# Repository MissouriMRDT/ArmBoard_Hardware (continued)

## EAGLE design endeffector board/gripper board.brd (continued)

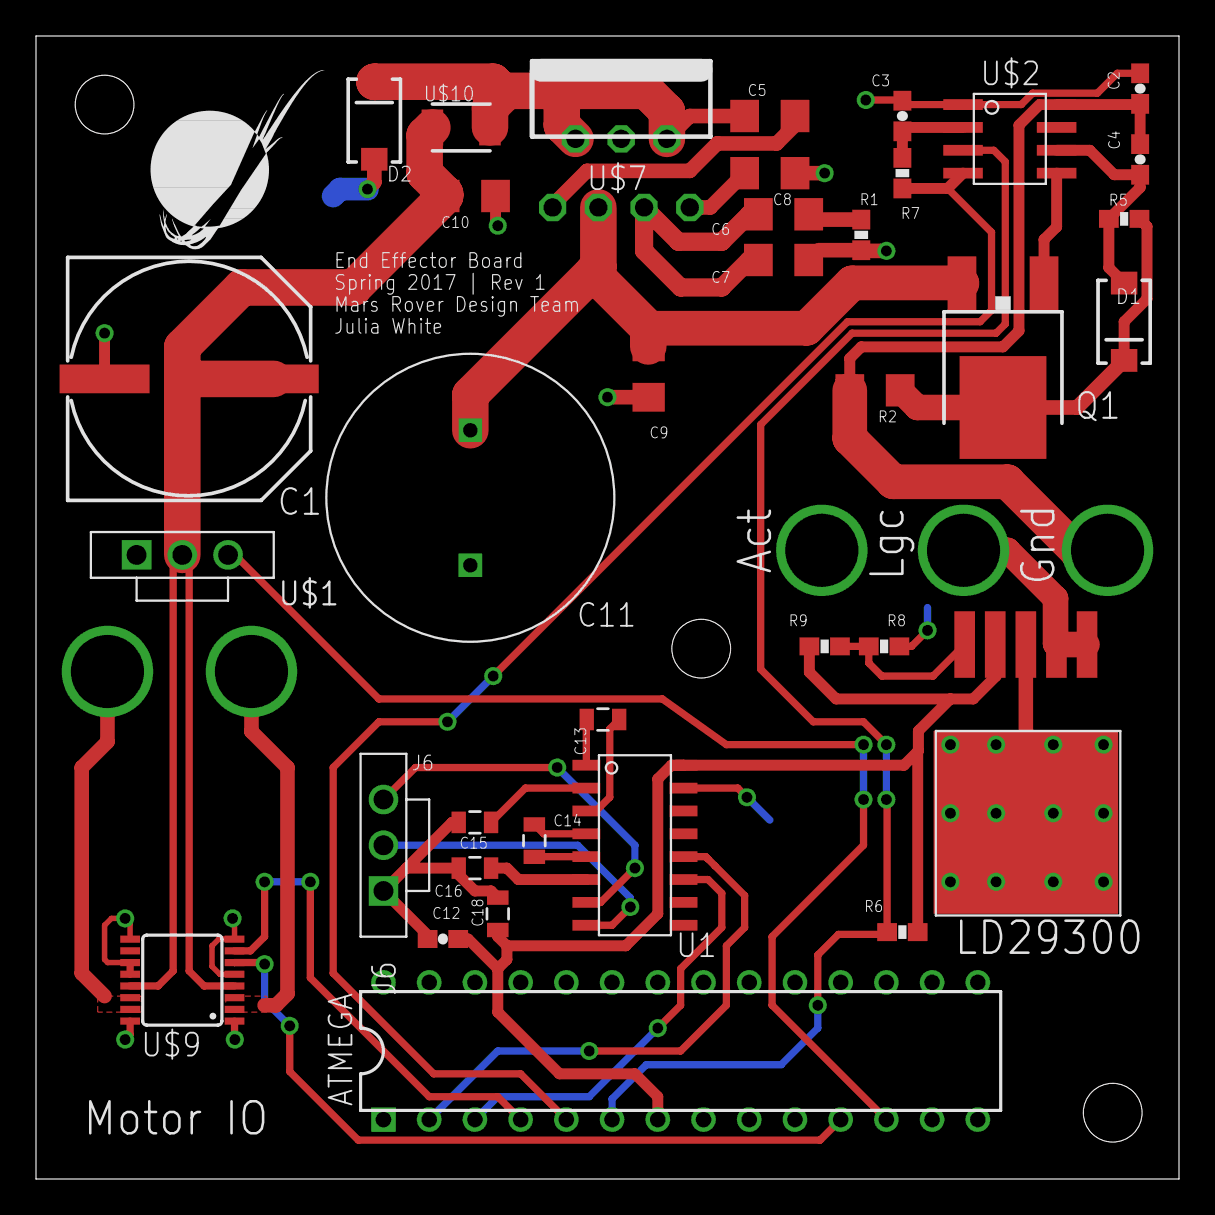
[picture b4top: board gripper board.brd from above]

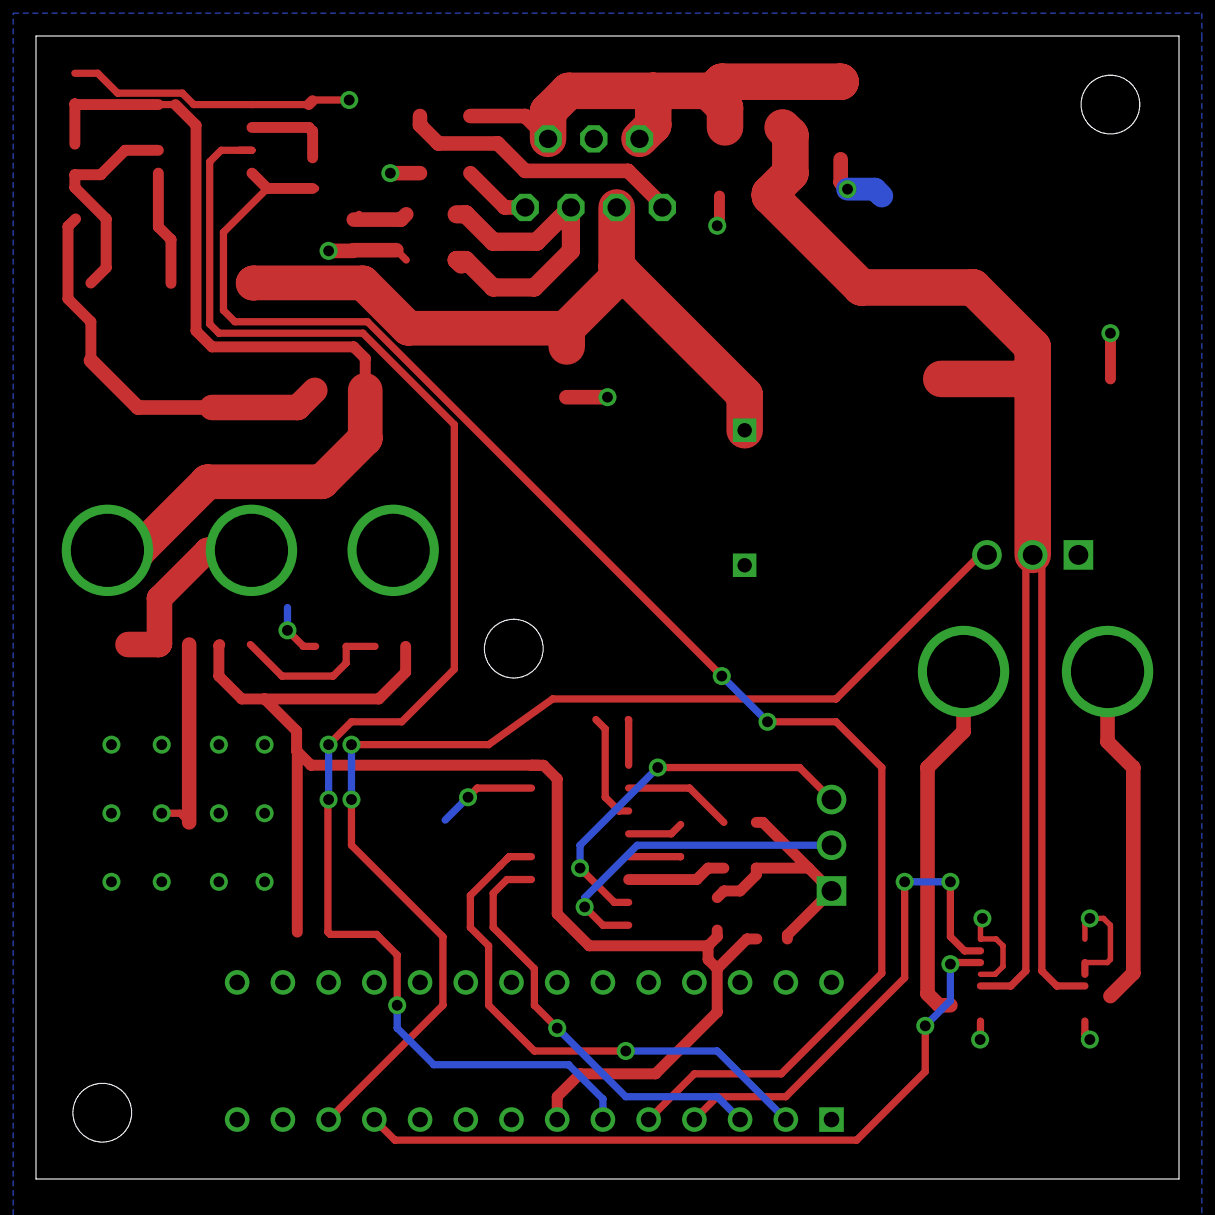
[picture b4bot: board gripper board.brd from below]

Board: 2 copper layers, 63.5 x 63.5 mm, 45 parts (6 on the bottom side), 33 nets.

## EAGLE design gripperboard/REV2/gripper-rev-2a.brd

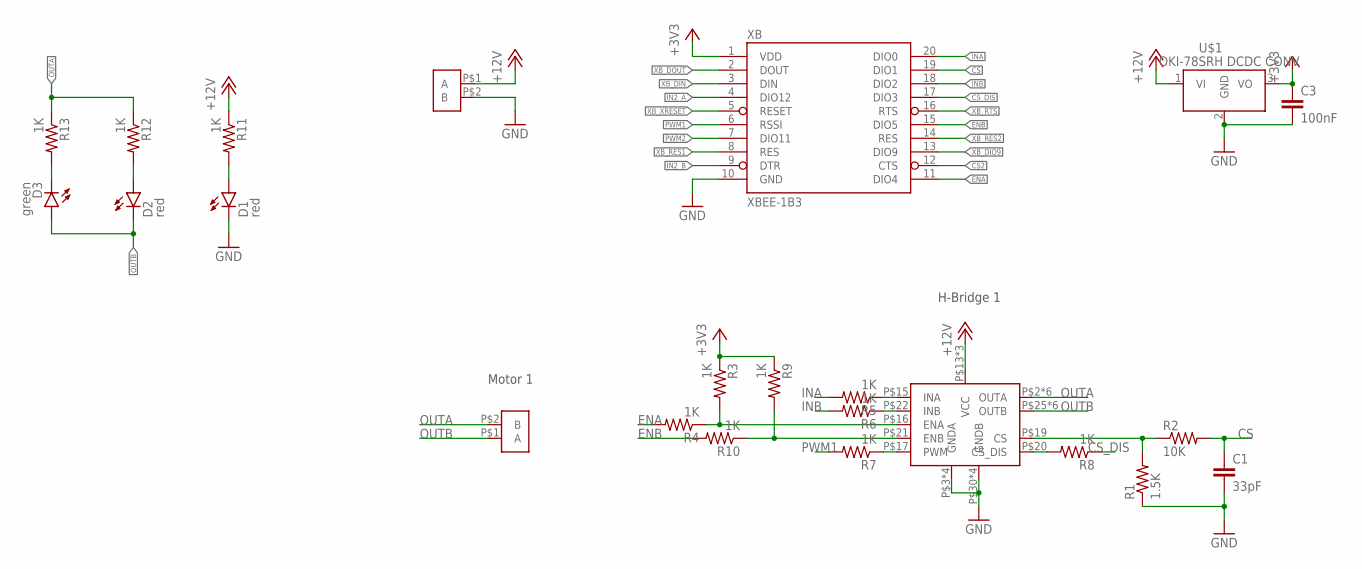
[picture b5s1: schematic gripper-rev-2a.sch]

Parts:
C1: 33pF; 0603-CAP
C3: 100nF; 0603-CAP
D1, D2: red; LED-0603
D3: green; LED-0603
R1: 1.5K; 0603-RES
R2: 10K; 0603-RES
R3, R4, R5, R6, R7, R8, R9, R10, R11, R12, R13: 1K; 0603-RES
U$1: Q_OKI-78SR; OKI-78SR_HORIZ
U$4: VNH5180A; POWERSSO-36_TP
U$6, U$8: TE_2POS_SCREW_TERM; TE_2POS-5MM_SCREW_TERM
XB: XBEE-1B3; XBEE-SMD

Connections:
+3V3: C3.1, R3.1, R9.1, U$1.3 (VO), XB.1 (VDD)
+12V: R11.1, U$1.1 (VI), U$4.P$13 (VCC), U$4.P$24 (VCC), U$4.SLUG1 (VCC), U$6.P$1 (A)
CS: C1.1, R2.2, XB.19 (DIO1)
CS2: XB.12 (CTS)
CS_DIS: R8.1, XB.17 (DIO3)
ENA: R4.2, XB.11 (DIO4)
ENB: R10.2, XB.15 (DIO5)
GND: C1.2, C3.2, D1.C, R1.1, U$1.2 (GND), U$4.P$3 (GNDA), U$4.P$4 (GNDA), U$4.P$6 (GNDA), U$4.P$7 (GNDA), U$4.P$30 (GNDB), U$4.P$31 (GNDB), U$4.P$33 (GNDB), U$4.P$34 (GNDB), U$6.P$2 (B), XB.10 (GND)
IN2_A: XB.4 (DIO12)
IN2_B: XB.9 (DTR)
INA: R5.2, XB.20 (DIO0)
INB: R6.2, XB.18 (DIO2)
unnamed: R5.1, U$4.P$15 (INA)
unnamed: R1.2, R2.1, U$4.P$19 (CS)
unnamed: R6.1, U$4.P$22 (INB)
unnamed: R7.1, U$4.P$17 (PWM)
unnamed: R3.2, R4.1, U$4.P$16 (ENA)
unnamed: R9.2, R10.1, U$4.P$21 (ENB)
unnamed: R8.2, U$4.P$20 (CS_DIS)
unnamed: D1.A, R11.2
unnamed: D2.A, R12.2
unnamed: D3.C, R13.2
OUTA: R12.1, R13.1, U$4.P$2 (OUTA), U$4.P$8 (OUTA), U$4.P$10 (OUTA), U$4.P$11 (OUTA), U$4.P$12 (OUTA), U$4.SLUG2 (OUTA), U$8.P$2 (B)
OUTB: D2.C, D3.A, U$4.P$25 (OUTB), U$4.P$26 (OUTB), U$4.P$27 (OUTB), U$4.P$29 (OUTB), U$4.P$35 (OUTB), U$4.SLUG3 (OUTB), U$8.P$1 (A)
PWM1: R7.2, XB.6 (RSSI)
PWM2: XB.7 (DIO11)
XB_DIN: XB.3 (DIN)
XB_DIO9: XB.13 (DIO9)
XB_RES1: XB.8 (RES)
XB_RES2: XB.14 (RES)
XB_RTS: XB.16 (RTS)
XB_XRESET: XB.5 (RESET)

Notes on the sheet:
H-Bridge 1
Motor 1

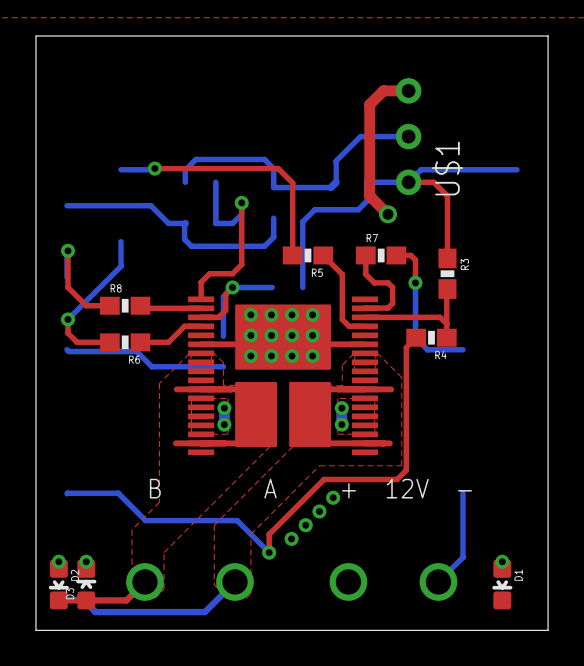
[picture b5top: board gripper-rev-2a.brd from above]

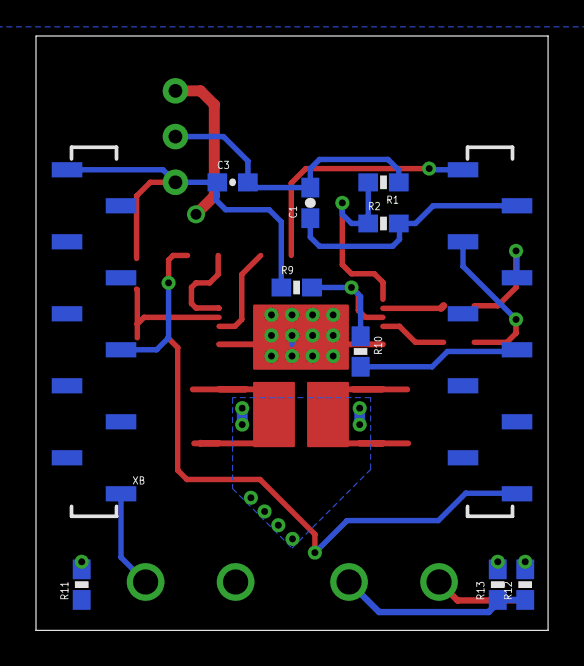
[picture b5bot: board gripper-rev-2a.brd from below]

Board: 2 copper layers, 28.4 x 33.0 mm, 23 parts (10 on the bottom side), 22 nets.

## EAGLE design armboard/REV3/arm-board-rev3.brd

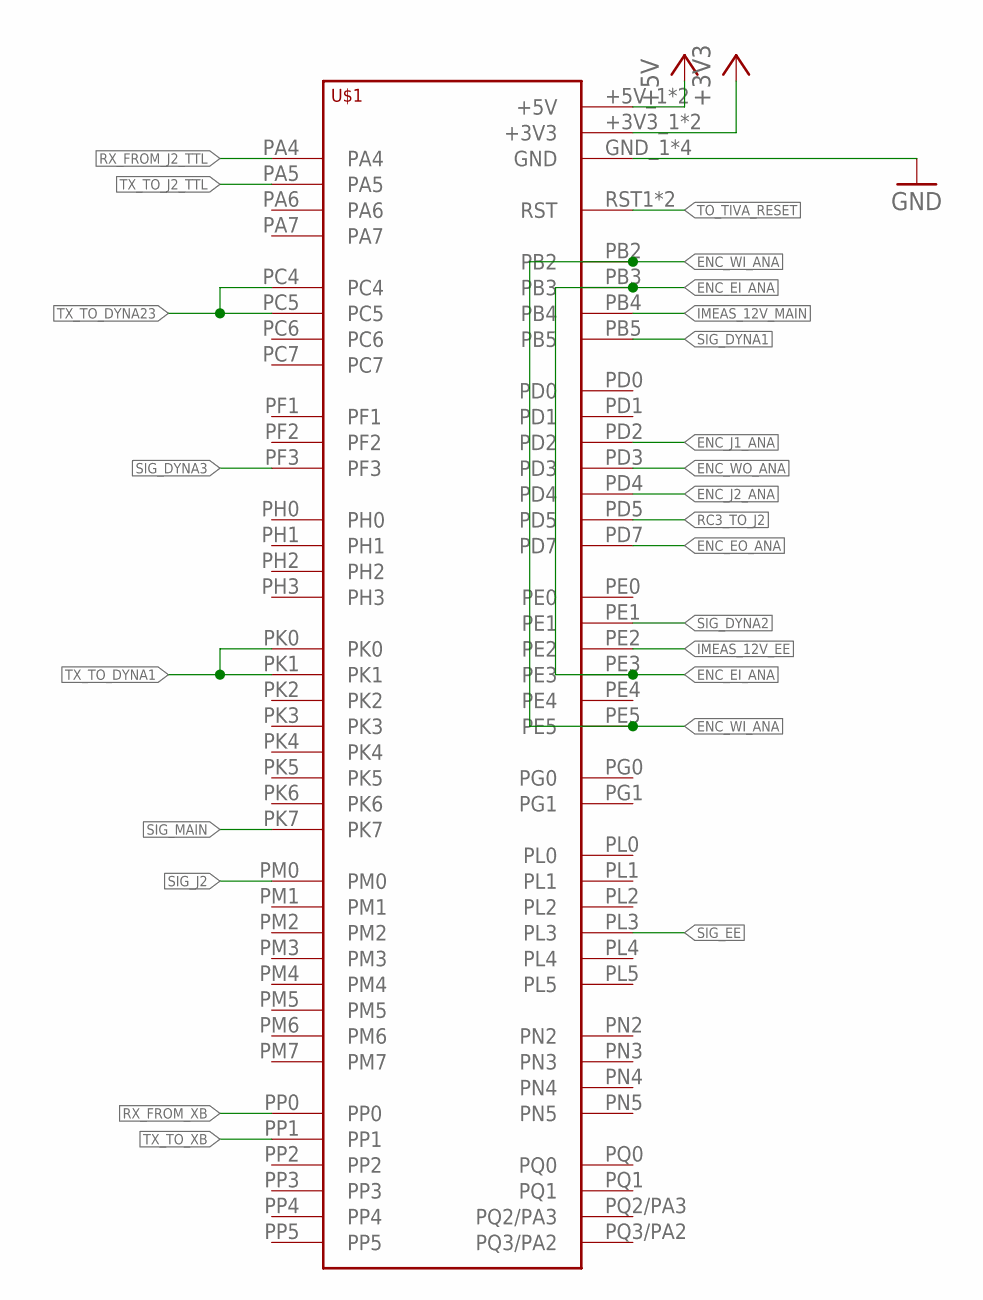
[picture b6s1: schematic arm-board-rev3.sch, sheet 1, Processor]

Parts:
U$1: TIVA-C-CONNECTED

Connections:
+3V3: U$1.+3V3_1 (+3V3), U$1.+3V3_2 (+3V3); also elsewhere on the board
+5V: U$1.+5V_1 (+5V), U$1.+5V_2 (+5V); also elsewhere on the board
ENC_EI_ANA: U$1.PB3, U$1.PE3; also elsewhere on the board
ENC_EO_ANA: U$1.PD7; also elsewhere on the board
ENC_J1_ANA: U$1.PD2; also elsewhere on the board
ENC_J2_ANA: U$1.PD4; also elsewhere on the board
ENC_WI_ANA: U$1.PB2, U$1.PE5; also elsewhere on the board
ENC_WO_ANA: U$1.PD3; also elsewhere on the board
GND: U$1.GND_1 (GND), U$1.GND_2 (GND), U$1.GND_3 (GND), U$1.GND_4 (GND); also elsewhere on the board
IMEAS_12V_EE: U$1.PE2; also elsewhere on the board
IMEAS_12V_MAIN: U$1.PB4; also elsewhere on the board
RC3_TO_J2: U$1.PD5; also elsewhere on the board
RX_FROM_J2_TTL: U$1.PA4; also elsewhere on the board
RX_FROM_XB: U$1.PP0; also elsewhere on the board
SIG_DYNA1: U$1.PB5; also elsewhere on the board
SIG_DYNA2: U$1.PE1; also elsewhere on the board
SIG_DYNA3: U$1.PF3; also elsewhere on the board
SIG_EE: U$1.PL3; also elsewhere on the board
SIG_J2: U$1.PM0; also elsewhere on the board
SIG_MAIN: U$1.PK7; also elsewhere on the board
TO_TIVA_RESET: U$1.RST1 (RST), U$1.RST_2 (RST); also elsewhere on the board
TX_TO_DYNA1: U$1.PK0, U$1.PK1; also elsewhere on the board
TX_TO_DYNA23: U$1.PC4, U$1.PC5; also elsewhere on the board
TX_TO_J2_TTL: U$1.PA5; also elsewhere on the board
TX_TO_XB: U$1.PP1; also elsewhere on the board

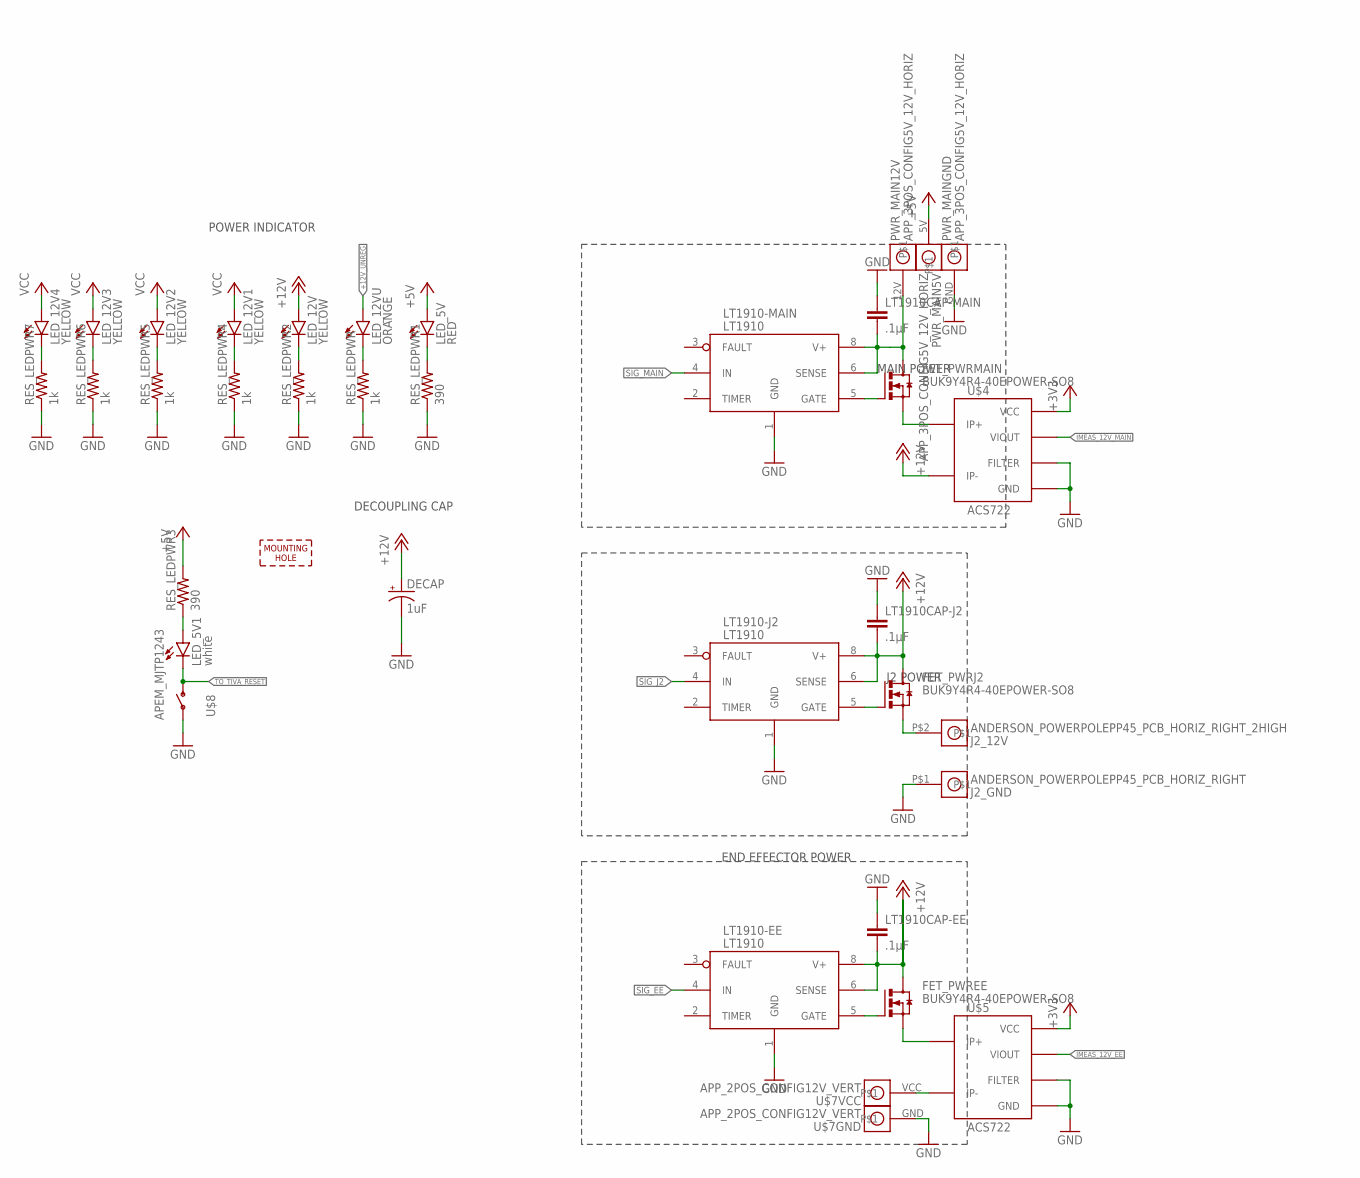
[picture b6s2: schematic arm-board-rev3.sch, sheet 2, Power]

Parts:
DECAP: 1uF; CPOL-RADIAL-100UF-25V
FET_PWREE: BUK9Y4R4-40EPOWER-SO8; POWER-SO8
FET_PWRJ2: BUK9Y4R4-40EPOWER-SO8; POWER-SO8
FET_PWRMAIN: BUK9Y4R4-40EPOWER-SO8; POWER-SO8
J2_12V: ANDERSON_POWERPOLEPP45_PCB_HORIZ_RIGHT_2HIGH; APP45_PCB_HORIZ_RIGHT_2HIGH
J2_GND: ANDERSON_POWERPOLEPP45_PCB_HORIZ_RIGHT; APP45_PCB_HORIZ_RIGHT
LED_5V: RED; LED-0603
LED_5V1: white; LED-1206
LED_12V, LED_12V1, LED_12V2, LED_12V3, LED_12V4: YELLOW; LED-0603
LED_12VU: ORANGE; LED-0603
LT1910-EE, LT1910-J2, LT1910-MAIN: LT1910; SO8
LT1910CAP-EE, LT1910CAP-J2, LT1910CAP-MAIN: .1µF; 0603-CAP
PWR_MAIN: APP_3POS_CONFIG5V_12V_HORIZ; APP45_5V_12V_HORIZ_CONFIG
RES_LEDPWR, RES_LEDPWR2, RES_LEDPWR4, RES_LEDPWR5, RES_LEDPWR6, RES_LEDPWR7: 1k; 0603-RES
RES_LEDPWR1, RES_LEDPWR3: 390; 0603-RES
U$3: MOUNTING_HOLE#6; #6_SCREW
U$4, U$5: ACS722; SO-08
U$7: APP_2POS_CONFIG12V_VERT; APP45_12V_VERT_CONFIG
U$8: APEM_MJTP1243

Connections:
+3V3: U$4.8 (VCC), U$5.8 (VCC); also elsewhere on the board
+5V: LED_5V.A, PWR_MAIN.5V, RES_LEDPWR3.2; also elsewhere on the board
+12V: DECAP.1 (+), FET_PWREE.5 (D), FET_PWREE.6 (D), FET_PWREE.7 (D), FET_PWREE.8 (D), FET_PWRJ2.5 (D), FET_PWRJ2.6 (D), FET_PWRJ2.7 (D), FET_PWRJ2.8 (D), LED_12V.A, LT1910-EE.6 (SENSE), LT1910-EE.8 (V+), LT1910-J2.6 (SENSE), LT1910-J2.8 (V+), LT1910CAP-EE.2, LT1910CAP-J2.2, U$4.3 (IP-), U$4.4 (IP-); also elsewhere on the board
+12V_UNREG: FET_PWRMAIN.5 (D), FET_PWRMAIN.6 (D), FET_PWRMAIN.7 (D), FET_PWRMAIN.8 (D), LED_12VU.A, LT1910-MAIN.6 (SENSE), LT1910-MAIN.8 (V+), LT1910CAP-MAIN.2, PWR_MAIN.12V
GATE-EE: FET_PWREE.4 (G), LT1910-EE.5 (GATE)
GATE-J2: FET_PWRJ2.4 (G), LT1910-J2.5 (GATE)
GATE-MAIN: FET_PWRMAIN.4 (G), LT1910-MAIN.5 (GATE)
GND: DECAP.2 (-), J2_GND.P$1, LT1910-EE.1 (GND), LT1910-J2.1 (GND), LT1910-MAIN.1 (GND), LT1910CAP-EE.1, LT1910CAP-J2.1, LT1910CAP-MAIN.1, PWR_MAIN.GND, RES_LEDPWR.1, RES_LEDPWR1.1, RES_LEDPWR2.1, RES_LEDPWR4.1, RES_LEDPWR5.1, RES_LEDPWR6.1, RES_LEDPWR7.1, U$4.5 (GND), U$4.6 (FILTER), U$5.5 (GND), U$5.6 (FILTER), U$7.GND, U$8.P$1; also elsewhere on the board
IMEAS_12V_EE: U$5.7 (VIOUT); also elsewhere on the board
IMEAS_12V_MAIN: U$4.7 (VIOUT); also elsewhere on the board
unnamed: LED_12V.C, RES_LEDPWR2.2
unnamed: LED_12VU.C, RES_LEDPWR.2
unnamed: LED_5V.C, RES_LEDPWR1.2
unnamed: LED_12V1.C, RES_LEDPWR4.2
unnamed: U$5.3 (IP-), U$5.4 (IP-), U$7.VCC
unnamed: LED_5V1.A, RES_LEDPWR3.1
unnamed: LED_12V2.C, RES_LEDPWR5.2
unnamed: LED_12V3.C, RES_LEDPWR6.2
unnamed: LED_12V4.C, RES_LEDPWR7.2
SIG_EE: LT1910-EE.4 (IN); also elsewhere on the board
SIG_J2: LT1910-J2.4 (IN); also elsewhere on the board
SIG_MAIN: LT1910-MAIN.4 (IN); also elsewhere on the board
SOURCE-DYNA1: LED_12V2.A; also elsewhere on the board
SOURCE-DYNA2: LED_12V3.A; also elsewhere on the board
SOURCE-DYNA3: LED_12V4.A; also elsewhere on the board
SOURCE-EE: FET_PWREE.1 (S), FET_PWREE.2 (S), FET_PWREE.3 (S), U$5.1 (IP+), U$5.2 (IP+)
SOURCE-J2: FET_PWRJ2.1 (S), FET_PWRJ2.2 (S), FET_PWRJ2.3 (S), J2_12V.P$2, LED_12V1.A
SOURCE-MAIN: FET_PWRMAIN.1 (S), FET_PWRMAIN.2 (S), FET_PWRMAIN.3 (S), U$4.1 (IP+), U$4.2 (IP+)
TO_TIVA_RESET: LED_5V1.C, U$8.P$2 (S); also elsewhere on the board

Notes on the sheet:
MAIN POWER
J2 POWER
END EFFECTOR POWER
POWER INDICATOR
DECOUPLING CAP

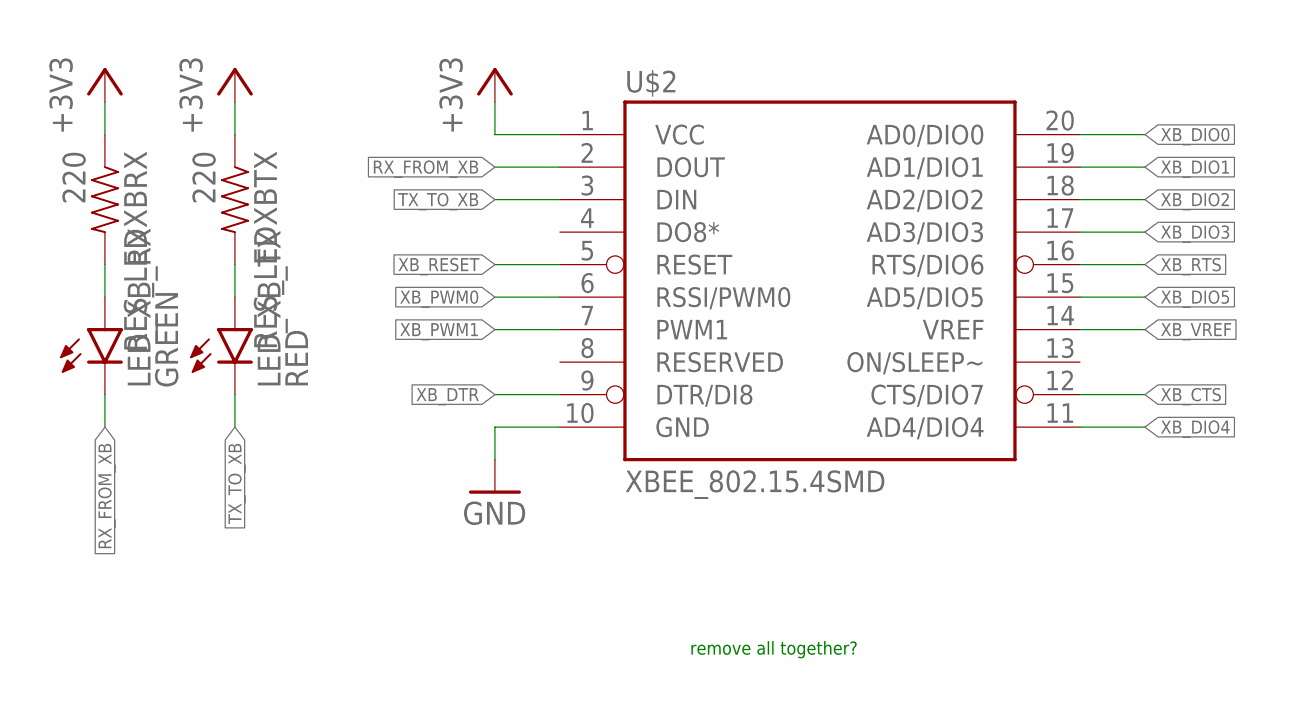
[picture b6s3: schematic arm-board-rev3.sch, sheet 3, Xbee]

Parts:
LED_XB_RX: GREEN; LED-0603
LED_XB_TX: RED; LED-0603
RES_LEDXBRX: 220; 0603-RES
RES_LEDXBTX: 220; 0603-RES
U$2: XBEE_802.15.4SMD; XBEE_802.15.4_SMD

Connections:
+3V3: RES_LEDXBRX.1, RES_LEDXBTX.1, U$2.1 (VCC); also elsewhere on the board
GND: U$2.10 (GND); also elsewhere on the board
unnamed: LED_XB_RX.A, RES_LEDXBRX.2
unnamed: LED_XB_TX.A, RES_LEDXBTX.2
RX_FROM_XB: LED_XB_RX.C, U$2.2 (DOUT); also elsewhere on the board
TX_TO_XB: LED_XB_TX.C, U$2.3 (DIN); also elsewhere on the board
XB_CTS: U$2.12 (CTS/DIO7)
XB_DIO0: U$2.20 (AD0/DIO0)
XB_DIO1: U$2.19 (AD1/DIO1)
XB_DIO2: U$2.18 (AD2/DIO2)
XB_DIO3: U$2.17 (AD3/DIO3)
XB_DIO4: U$2.11 (AD4/DIO4)
XB_DIO5: U$2.15 (AD5/DIO5)
XB_DTR: U$2.9 (DTR/DI8)
XB_PWM0: U$2.6 (RSSI/PWM0)
XB_PWM1: U$2.7 (PWM1)
XB_RESET: U$2.5 (RESET)
XB_RTS: U$2.16 (RTS/DIO6)
XB_VREF: U$2.14 (VREF)

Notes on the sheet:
remove all together?

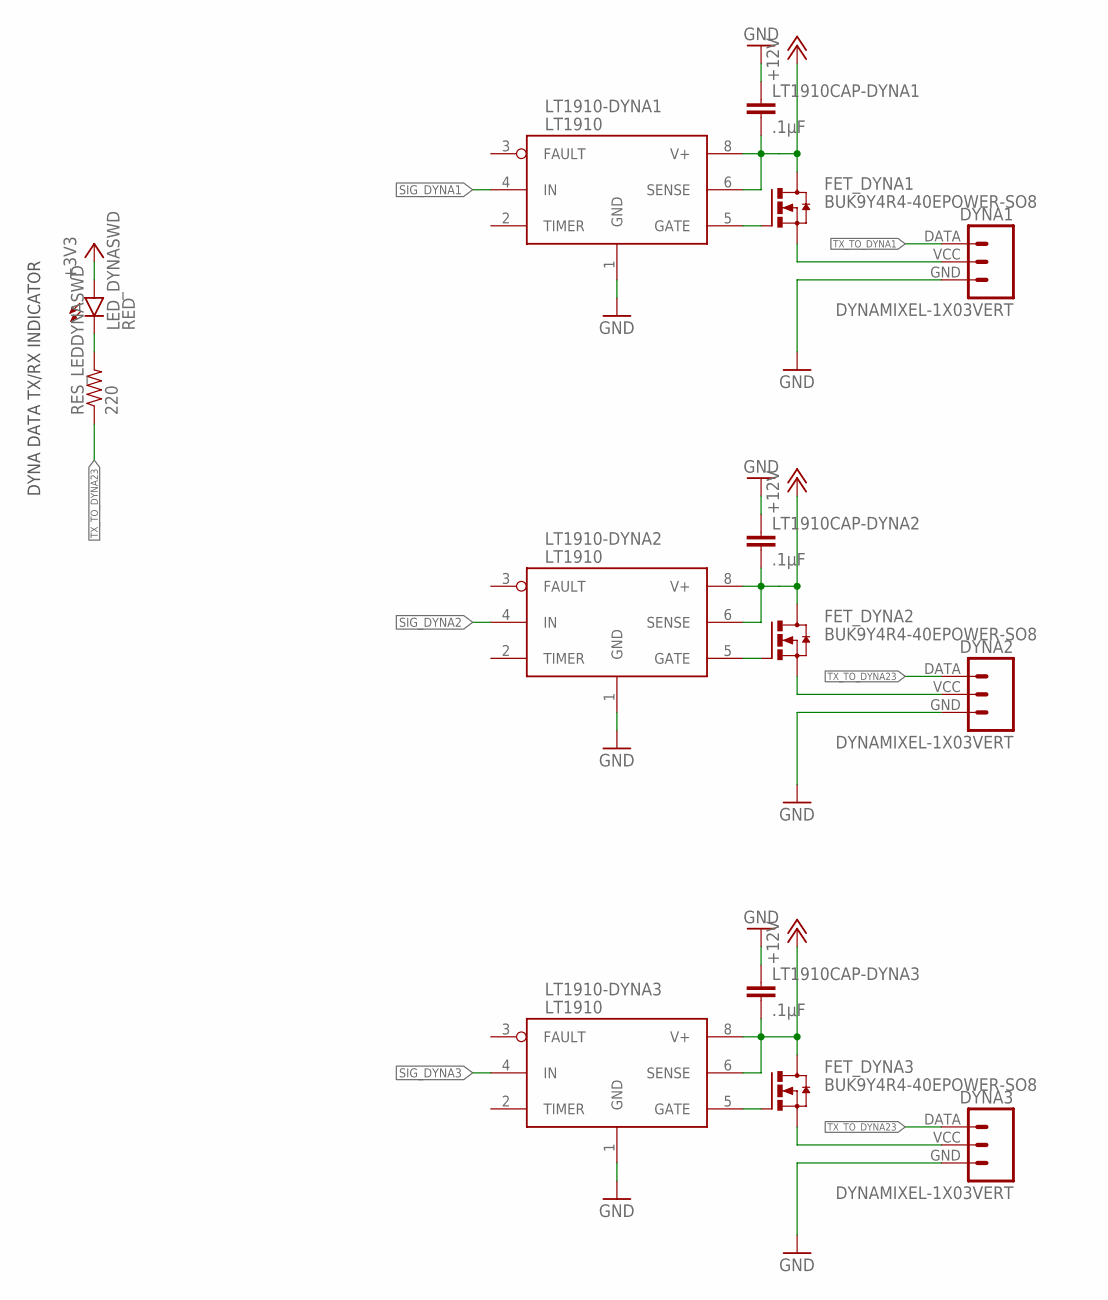
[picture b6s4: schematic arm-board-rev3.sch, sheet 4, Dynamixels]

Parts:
DYNA1, DYNA2, DYNA3: DYNAMIXEL-1X03VERT; MLX-SPOX5267-3PIN
FET_DYNA1, FET_DYNA2, FET_DYNA3: BUK9Y4R4-40EPOWER-SO8; POWER-SO8
LED_DYNASWD: RED; LED-0603
LT1910-DYNA1, LT1910-DYNA2, LT1910-DYNA3: LT1910; SO8
LT1910CAP-DYNA1, LT1910CAP-DYNA2, LT1910CAP-DYNA3: .1µF; 0603-CAP
RES_LEDDYNASWD: 220; 0603-RES

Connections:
+3V3: LED_DYNASWD.A; also elsewhere on the board
+12V: FET_DYNA1.5 (D), FET_DYNA1.6 (D), FET_DYNA1.7 (D), FET_DYNA1.8 (D), FET_DYNA2.5 (D), FET_DYNA2.6 (D), FET_DYNA2.7 (D), FET_DYNA2.8 (D), FET_DYNA3.5 (D), FET_DYNA3.6 (D), FET_DYNA3.7 (D), FET_DYNA3.8 (D), LT1910-DYNA1.6 (SENSE), LT1910-DYNA1.8 (V+), LT1910-DYNA2.6 (SENSE), LT1910-DYNA2.8 (V+), LT1910-DYNA3.6 (SENSE), LT1910-DYNA3.8 (V+), LT1910CAP-DYNA1.2, LT1910CAP-DYNA2.2, LT1910CAP-DYNA3.2; also elsewhere on the board
GATE-DYNA1: FET_DYNA1.4 (G), LT1910-DYNA1.5 (GATE)
GATE-DYNA2: FET_DYNA2.4 (G), LT1910-DYNA2.5 (GATE)
GATE-DYNA3: FET_DYNA3.4 (G), LT1910-DYNA3.5 (GATE)
GND: DYNA1.GND, DYNA2.GND, DYNA3.GND, LT1910-DYNA1.1 (GND), LT1910-DYNA2.1 (GND), LT1910-DYNA3.1 (GND), LT1910CAP-DYNA1.1, LT1910CAP-DYNA2.1, LT1910CAP-DYNA3.1; also elsewhere on the board
unnamed: LED_DYNASWD.C, RES_LEDDYNASWD.2
SIG_DYNA1: LT1910-DYNA1.4 (IN); also elsewhere on the board
SIG_DYNA2: LT1910-DYNA2.4 (IN); also elsewhere on the board
SIG_DYNA3: LT1910-DYNA3.4 (IN); also elsewhere on the board
SOURCE-DYNA1: DYNA1.VCC, FET_DYNA1.1 (S), FET_DYNA1.2 (S), FET_DYNA1.3 (S); also elsewhere on the board
SOURCE-DYNA2: DYNA2.VCC, FET_DYNA2.1 (S), FET_DYNA2.2 (S), FET_DYNA2.3 (S); also elsewhere on the board
SOURCE-DYNA3: DYNA3.VCC, FET_DYNA3.1 (S), FET_DYNA3.2 (S), FET_DYNA3.3 (S); also elsewhere on the board
TX_TO_DYNA1: DYNA1.DATA; also elsewhere on the board
TX_TO_DYNA23: DYNA2.DATA, DYNA3.DATA, RES_LEDDYNASWD.1; also elsewhere on the board

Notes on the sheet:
DYNA DATA TX/RX INDICATOR

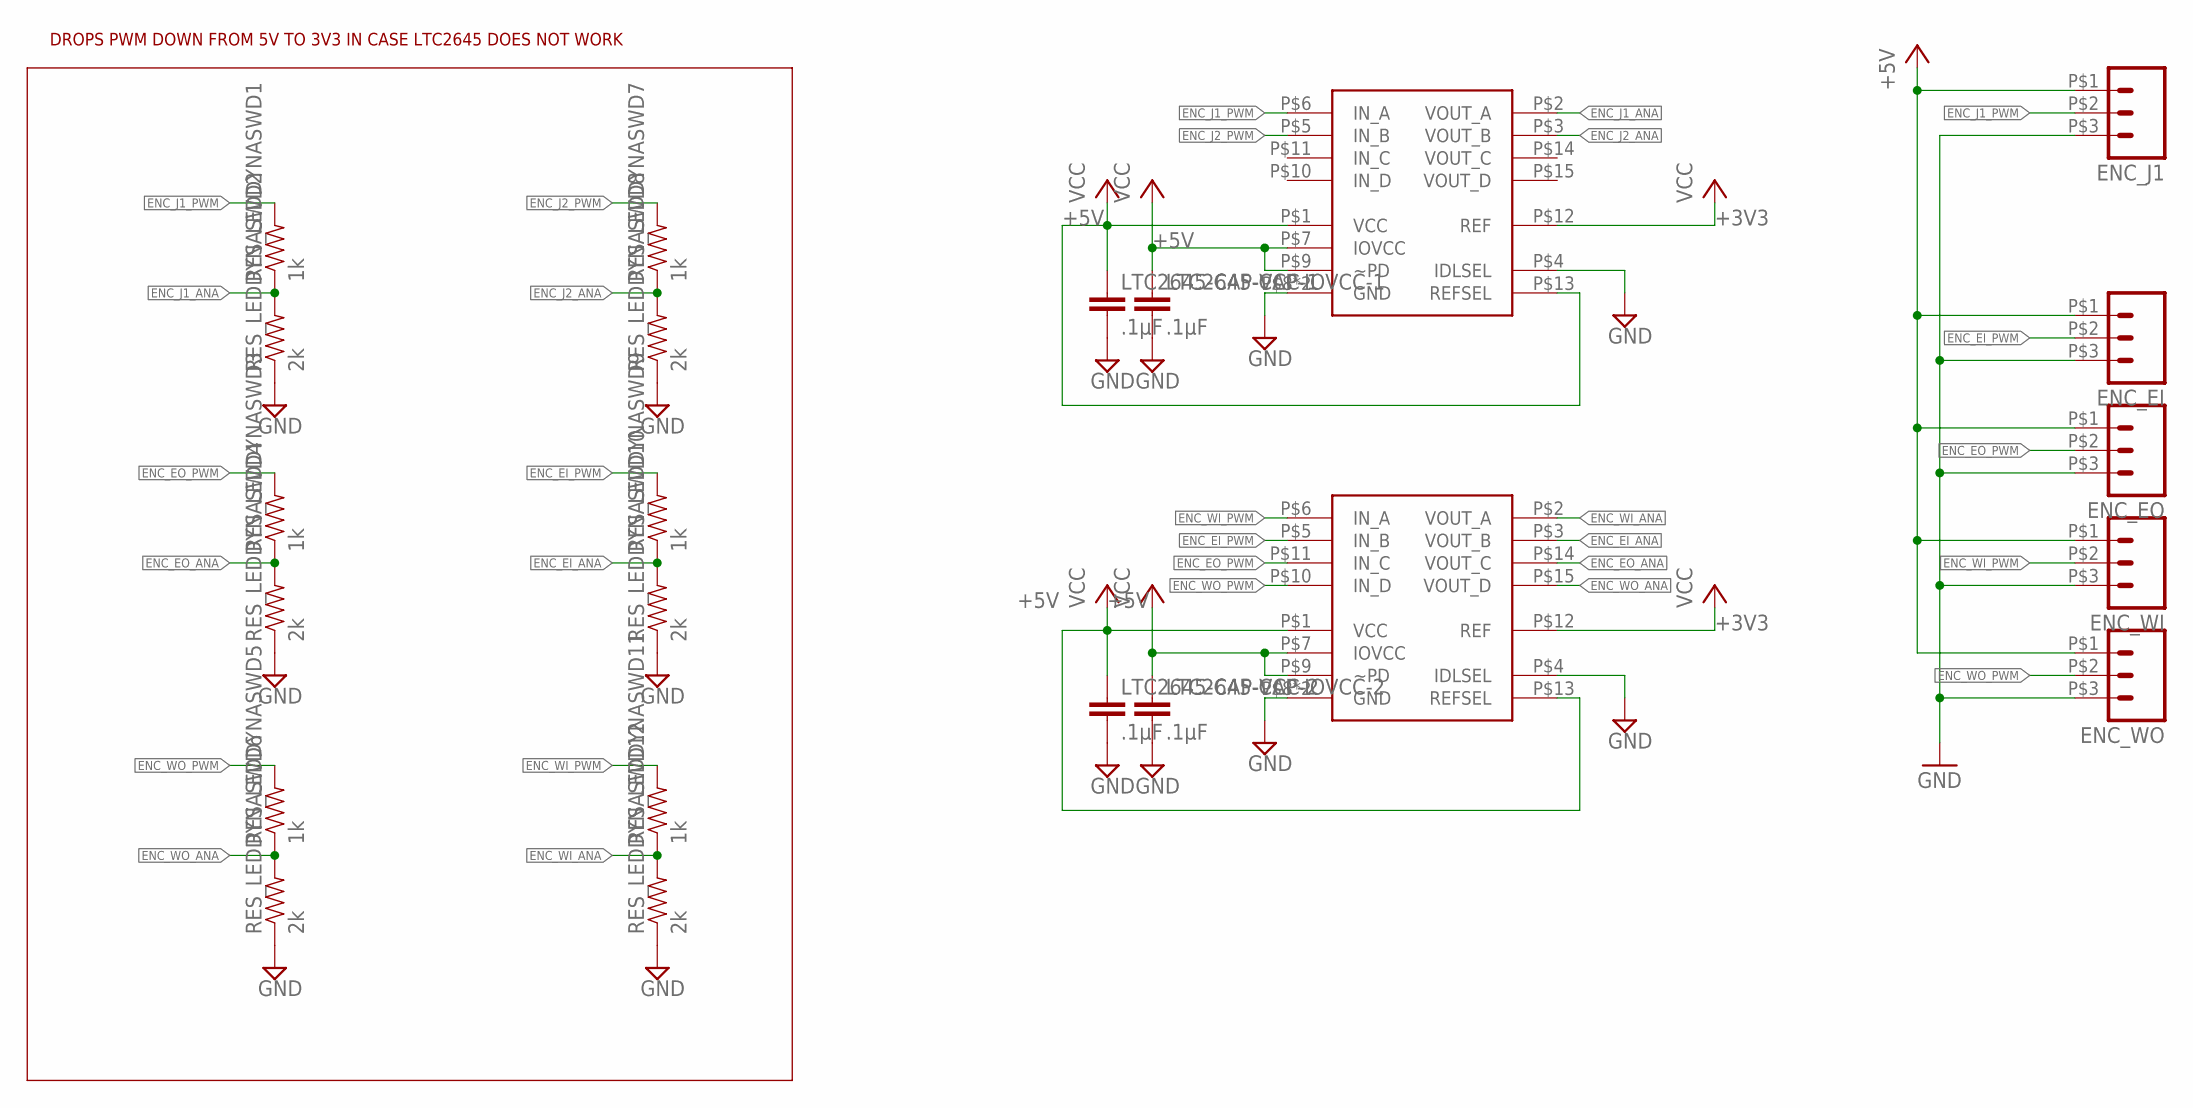
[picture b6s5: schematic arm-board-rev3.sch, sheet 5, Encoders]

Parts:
ENC_EI: M03VERT; MOLEX0436500328
ENC_EO: M03VERT; MOLEX0436500328
ENC_J1: M03VERT; MOLEX0436500328
ENC_WI: M03VERT; MOLEX0436500328
ENC_WO: M03VERT; MOLEX0436500328
LTC2645-CAP-IOVCC-1, LTC2645-CAP-IOVCC-2, LTC2645-CAP-VCC-1, LTC2645-CAP-VCC-2: .1µF; 0603-CAP
RES_LEDDYNASWD1, RES_LEDDYNASWD3, RES_LEDDYNASWD5, RES_LEDDYNASWD7, RES_LEDDYNASWD9, RES_LEDDYNASWD11: 1k; 0603-RES
RES_LEDDYNASWD2, RES_LEDDYNASWD4, RES_LEDDYNASWD6, RES_LEDDYNASWD8, RES_LEDDYNASWD10, RES_LEDDYNASWD12: 2k; 0603-RES
U$9, U$11: LTC2645; MSOP16

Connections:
+3V3: U$9.P$12 (REF), U$11.P$12 (REF); also elsewhere on the board
+5V: ENC_EI.P$1 (1), ENC_EO.P$1 (1), ENC_J1.P$1 (1), ENC_WI.P$1 (1), ENC_WO.P$1 (1), LTC2645-CAP-IOVCC-1.1, LTC2645-CAP-IOVCC-2.1, LTC2645-CAP-VCC-1.1, LTC2645-CAP-VCC-2.1, U$9.P$1 (VCC), U$9.P$7 (IOVCC), U$9.P$9 (~PD), U$9.P$13 (REFSEL), U$11.P$1 (VCC), U$11.P$7 (IOVCC), U$11.P$9 (~PD), U$11.P$13 (REFSEL); also elsewhere on the board
ENC_EI_ANA: RES_LEDDYNASWD9.1, RES_LEDDYNASWD10.2, U$11.P$3 (VOUT_B); also elsewhere on the board
ENC_EI_PWM: ENC_EI.P$2 (2), RES_LEDDYNASWD9.2, U$11.P$5 (IN_B)
ENC_EO_ANA: RES_LEDDYNASWD3.1, RES_LEDDYNASWD4.2, U$11.P$14 (VOUT_C); also elsewhere on the board
ENC_EO_PWM: ENC_EO.P$2 (2), RES_LEDDYNASWD3.2, U$11.P$11 (IN_C)
ENC_J1_ANA: RES_LEDDYNASWD1.1, RES_LEDDYNASWD2.2, U$9.P$2 (VOUT_A); also elsewhere on the board
ENC_J1_PWM: ENC_J1.P$2 (2), RES_LEDDYNASWD1.2, U$9.P$6 (IN_A)
ENC_J2_ANA: RES_LEDDYNASWD7.1, RES_LEDDYNASWD8.2, U$9.P$3 (VOUT_B); also elsewhere on the board
ENC_J2_PWM: RES_LEDDYNASWD7.2, U$9.P$5 (IN_B); also elsewhere on the board
ENC_WI_ANA: RES_LEDDYNASWD11.1, RES_LEDDYNASWD12.2, U$11.P$2 (VOUT_A); also elsewhere on the board
ENC_WI_PWM: ENC_WI.P$2 (2), RES_LEDDYNASWD11.2, U$11.P$6 (IN_A)
ENC_WO_ANA: RES_LEDDYNASWD5.1, RES_LEDDYNASWD6.2, U$11.P$15 (VOUT_D); also elsewhere on the board
ENC_WO_PWM: ENC_WO.P$2 (2), RES_LEDDYNASWD5.2, U$11.P$10 (IN_D)
GND: ENC_EI.P$3 (3), ENC_EO.P$3 (3), ENC_J1.P$3 (3), ENC_WI.P$3 (3), ENC_WO.P$3 (3), LTC2645-CAP-IOVCC-1.2, LTC2645-CAP-IOVCC-2.2, LTC2645-CAP-VCC-1.2, LTC2645-CAP-VCC-2.2, RES_LEDDYNASWD2.1, RES_LEDDYNASWD4.1, RES_LEDDYNASWD6.1, RES_LEDDYNASWD8.1, RES_LEDDYNASWD10.1, RES_LEDDYNASWD12.1, U$9.P$4 (IDLSEL), U$9.P$8 (GND), U$9.P$16 (GND), U$11.P$4 (IDLSEL), U$11.P$8 (GND), U$11.P$16 (GND); also elsewhere on the board

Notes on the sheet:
DROPS PWM DOWN FROM 5V TO 3V3 IN CASE LTC2645 DOES NOT WORK

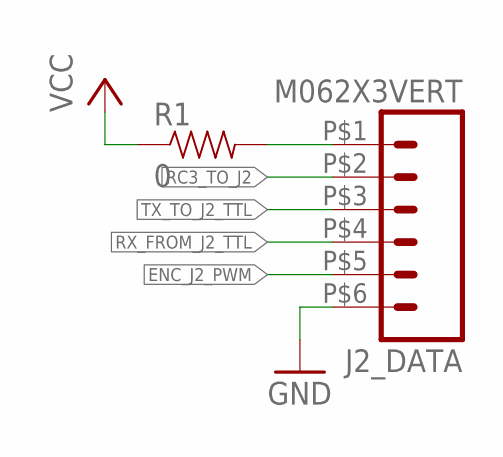
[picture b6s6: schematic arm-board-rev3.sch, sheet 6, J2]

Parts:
J2_DATA: M062X3VERT; MOLEX_0430450627
R1: 0; 0603-RES

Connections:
+5V: R1.1; also elsewhere on the board
ENC_J2_PWM: J2_DATA.P$5 (5); also elsewhere on the board
GND: J2_DATA.P$6 (6); also elsewhere on the board
unnamed: J2_DATA.P$1 (1), R1.2
RC3_TO_J2: J2_DATA.P$2 (2); also elsewhere on the board
RX_FROM_J2_TTL: J2_DATA.P$4 (4); also elsewhere on the board
TX_TO_J2_TTL: J2_DATA.P$3 (3); also elsewhere on the board

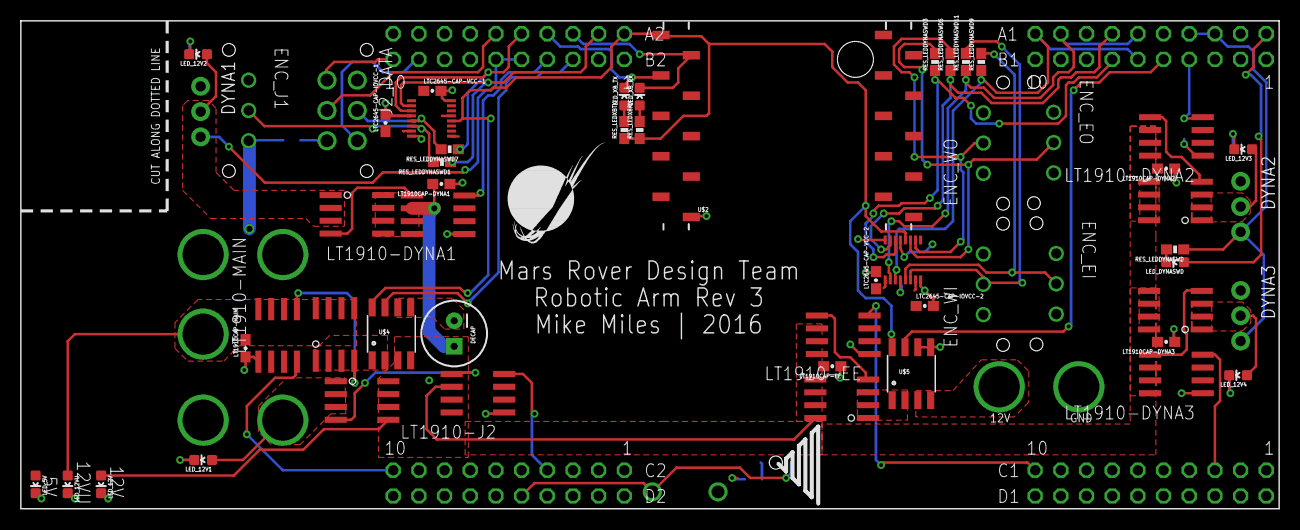
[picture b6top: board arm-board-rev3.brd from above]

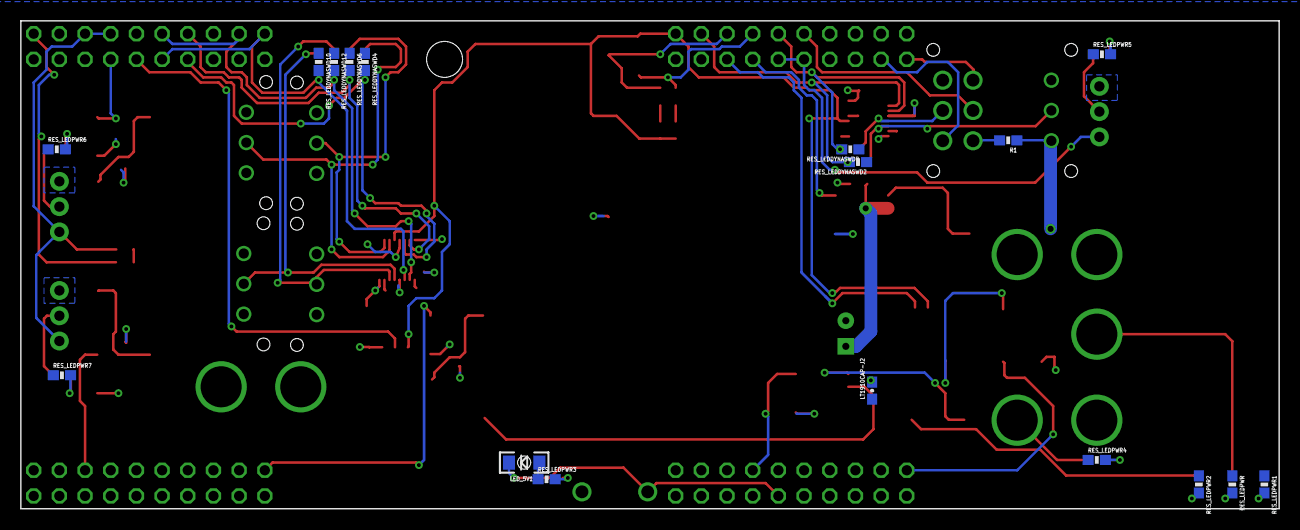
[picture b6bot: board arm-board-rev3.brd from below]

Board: 2 copper layers, 124.5 x 48.3 mm, 80 parts (17 on the bottom side), 58 nets.

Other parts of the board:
U$6: MRDT_LOGO
